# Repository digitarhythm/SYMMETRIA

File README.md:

# SYMMETRIA
TReK 40Plus SYMMETRIA KiCAD Project

[Firmware repository](https://github.com/digitarhythm/qmk_firmware/tree/digitarhythm/keyboards/trek/symmetria)

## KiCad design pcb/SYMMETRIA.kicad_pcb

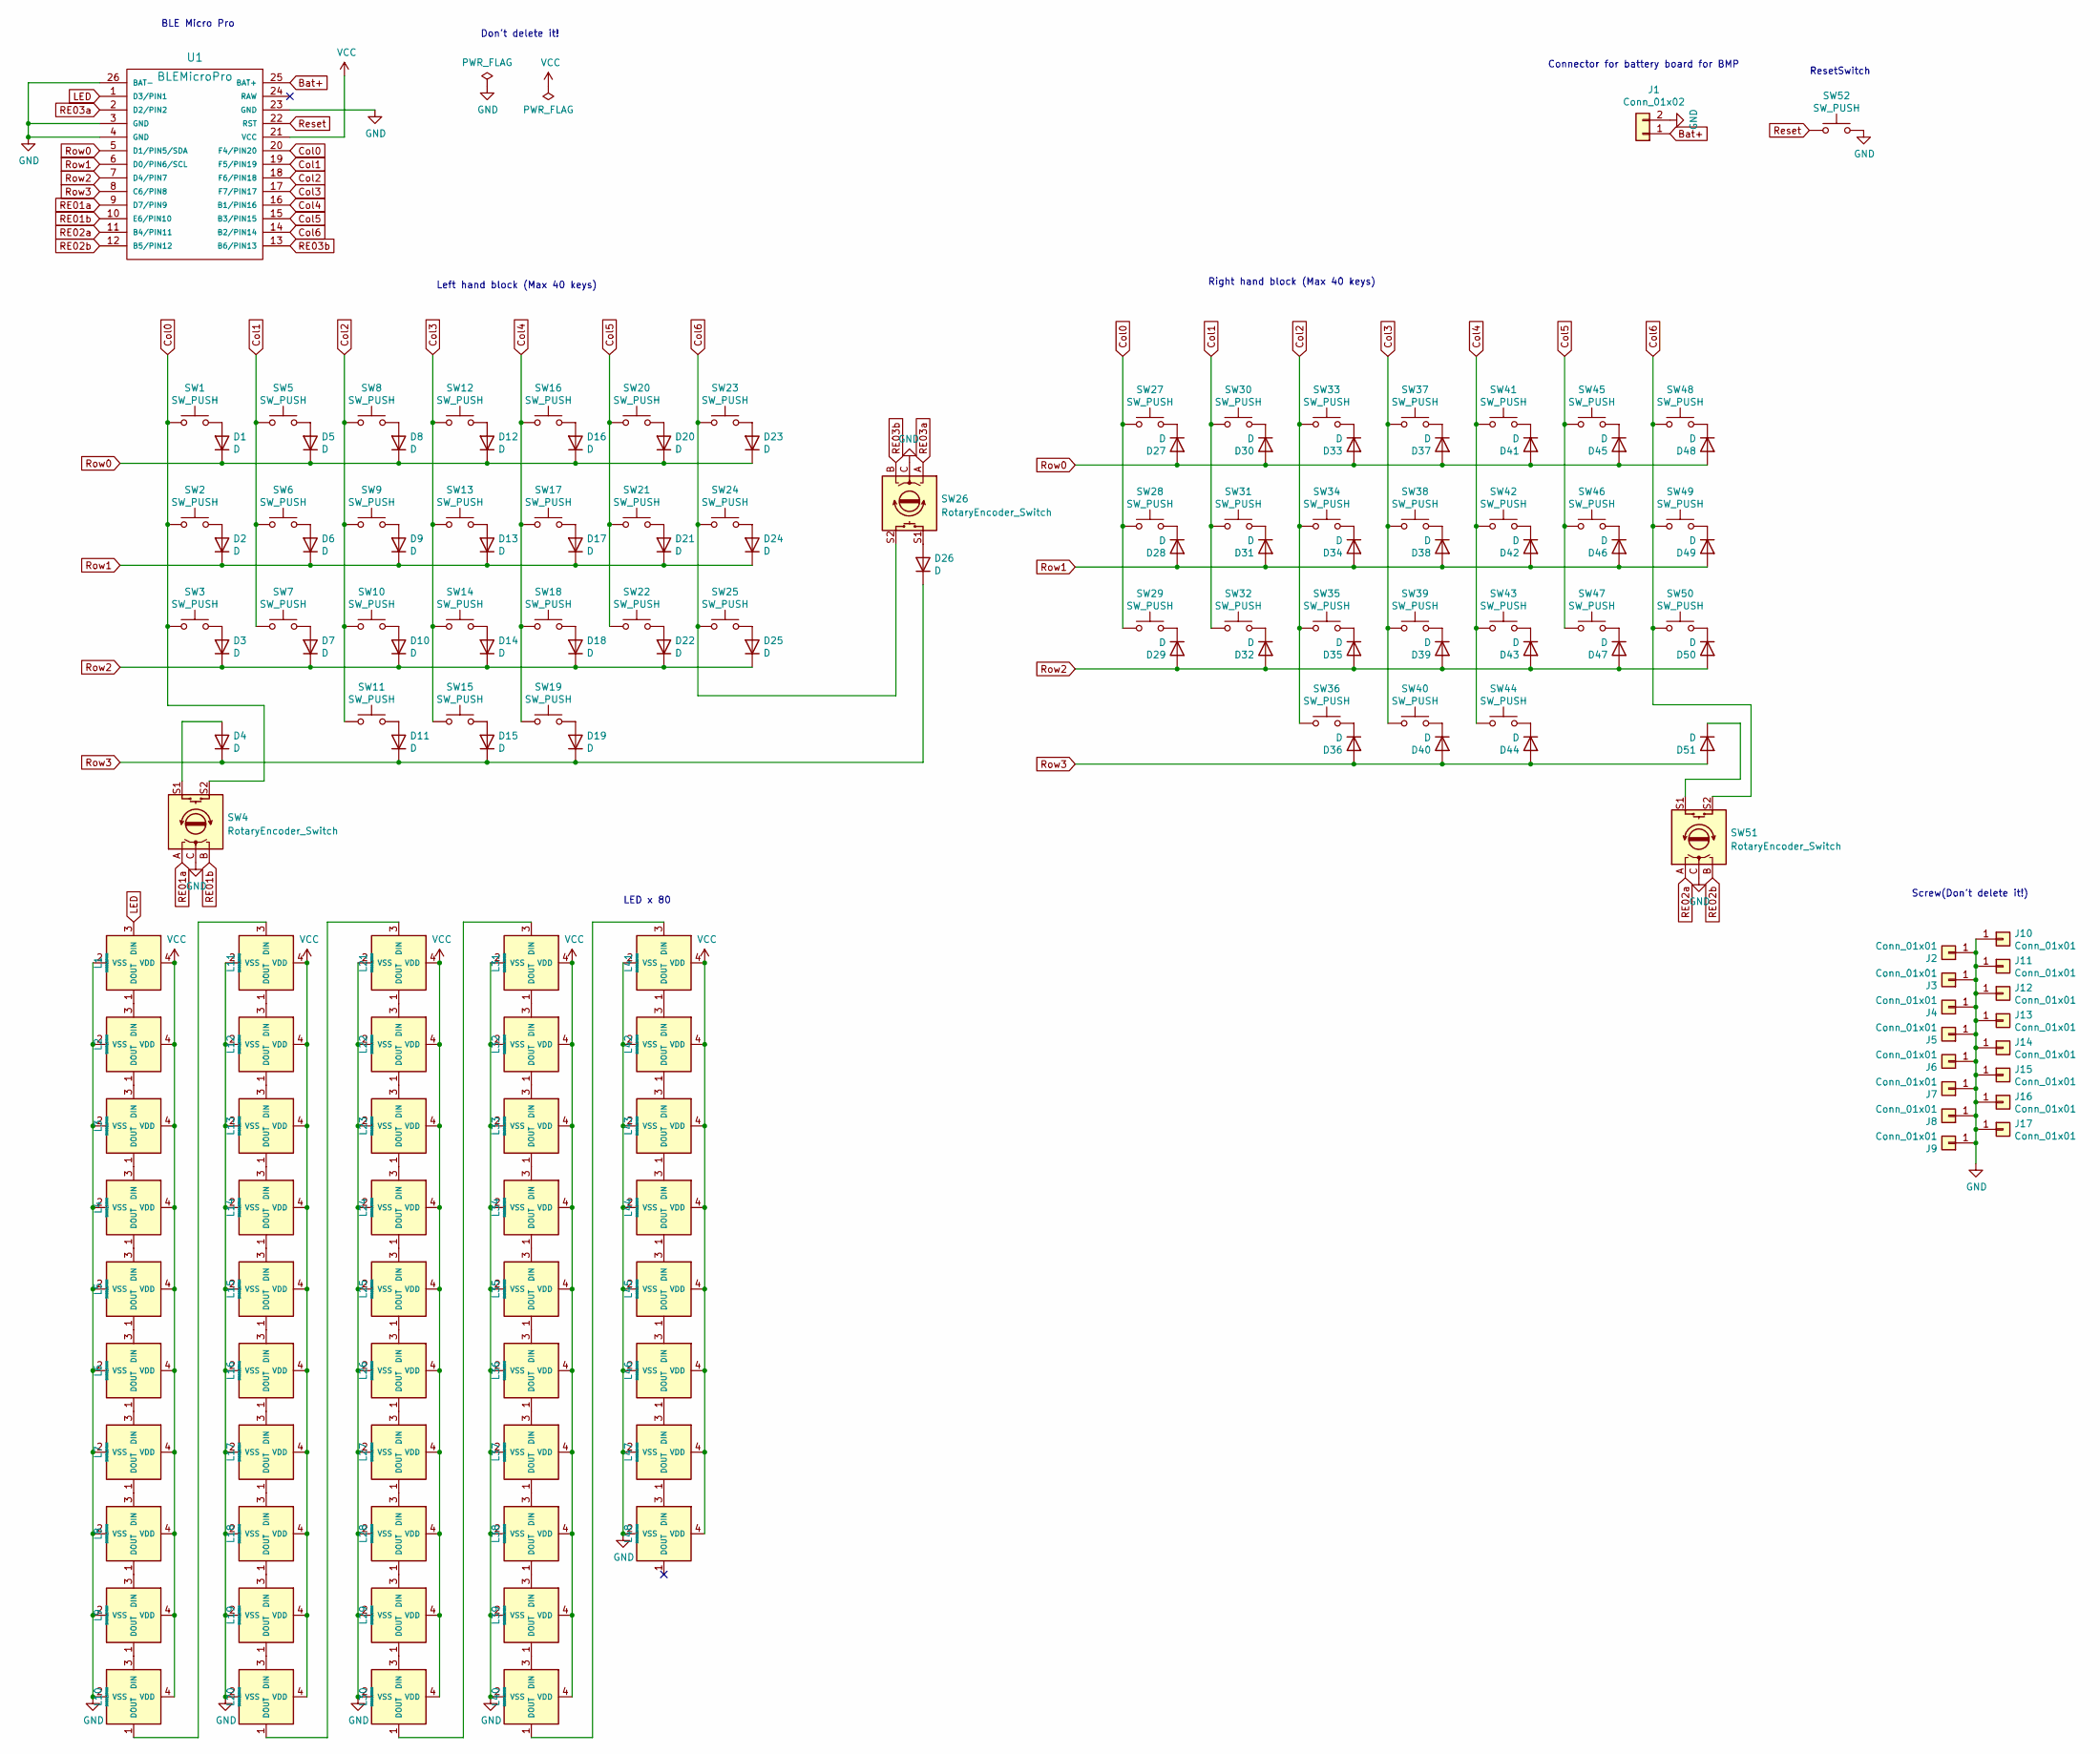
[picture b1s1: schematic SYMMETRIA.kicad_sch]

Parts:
D1, D2, D3, D4, D5, D6, D7, D8, D9, D10, D11, D12, D13, D14, D15, D16, D17, D18, D19, D20, D21, D22, D23, D24, D25, D26, D27, D28, D29, D30, D31, D32, D33, D34, D35, D36, D37, D38, D39, D40, D41, D42, D43, D44, D45, D46, D47, D48, D49, D50, D51: D; Diode_SMD
J1: Conn_01x02; Battery_XH2.5_GL_PCB
J2, J3, J4, J5, J6, J7: Conn_01x01; m2_Screw_Hole_EdgeCuts
J8, J9, J10, J11, J12, J13, J14, J15, J16, J17: Conn_01x01; m2_Screw_Hole_Fab
L1, L2, L3, L4, L5, L6, L7, L8, L9, L10, L11, L12, L13, L14, L15, L16, L17, L18, L19, L20, L21, L22, L23, L24, L25, L26, L27, L28, L29, L30, L31, L32, L33, L34, L35, L36, L37, L38, L39, L40, L41, L42, L43, L44, L45, L46, L47, L48: SK6812MINI; LED_SK6812MINI-E_BL
SW1, SW5, SW6, SW7, SW8, SW9, SW10, SW12, SW13, SW14, SW16, SW17, SW18, SW20, SW21, SW22, SW23, SW24, SW25, SW27, SW28, SW29, SW30, SW31, SW32, SW33, SW34, SW35, SW37, SW38, SW39, SW41, SW42, SW43, SW45, SW46, SW47, SW48: SW_PUSH; CherryMX_Hotswap_1u
SW2, SW11, SW19, SW36, SW44, SW49: SW_PUSH; CherryMX_Hotswap_1.25u
SW3, SW15, SW40, SW50: SW_PUSH; CherryMX_Hotswap_1.75u
SW4, SW51: RotaryEncoder_Switch; RotaryEncoder_EC12E
SW26: RotaryEncoder_Switch; SW_Cherry_MX_1.00u_Kailh_EC12
SW52: SW_PUSH; ResetSW
U1: BLEMicroPro; Micon_BMP_GL

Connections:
Bat+: J1.1, U1.25 (BAT+)
Col0: SW1.1, SW2.1, SW3.1, SW4.S2, SW27.1, SW28.1, SW29.1, U1.20 (F4/PIN20)
Col1: SW5.1, SW6.1, SW7.1, SW30.1, SW31.1, SW32.1, U1.19 (F5/PIN19)
Col2: SW8.1, SW9.1, SW10.1, SW11.1, SW33.1, SW34.1, SW35.1, SW36.1, U1.18 (F6/PIN18)
Col3: SW12.1, SW13.1, SW14.1, SW15.1, SW37.1, SW38.1, SW39.1, SW40.1, U1.17 (F7/PIN17)
Col4: SW16.1, SW17.1, SW18.1, SW19.1, SW41.1, SW42.1, SW43.1, SW44.1, U1.16 (B1/PIN16)
Col5: SW20.1, SW21.1, SW22.1, SW45.1, SW46.1, SW47.1, U1.15 (B3/PIN15)
Col6: SW23.1, SW24.1, SW25.1, SW26.S2, SW48.1, SW49.1, SW50.1, SW51.S2, U1.14 (B2/PIN14)
GND: J1.2, J2.1, J3.1, J4.1, J5.1, J6.1, J7.1, J8.1, J9.1, J10.1, J11.1, J12.1, J13.1, J14.1, J15.1, J16.1, J17.1, L1.2 (VSS), L2.2 (VSS), L3.2 (VSS), L4.2 (VSS), L5.2 (VSS), L6.2 (VSS), L7.2 (VSS), L8.2 (VSS), L9.2 (VSS), L10.2 (VSS), L11.2 (VSS), L12.2 (VSS), L13.2 (VSS), L14.2 (VSS), L15.2 (VSS), L16.2 (VSS), L17.2 (VSS), L18.2 (VSS), L19.2 (VSS), L20.2 (VSS), L21.2 (VSS), L22.2 (VSS), L23.2 (VSS), L24.2 (VSS), L25.2 (VSS), L26.2 (VSS), L27.2 (VSS), L28.2 (VSS), L29.2 (VSS), L30.2 (VSS), L31.2 (VSS), L32.2 (VSS), L33.2 (VSS), L34.2 (VSS), L35.2 (VSS), L36.2 (VSS), L37.2 (VSS), L38.2 (VSS), L39.2 (VSS), L40.2 (VSS), L41.2 (VSS), L42.2 (VSS), L43.2 (VSS), L44.2 (VSS), L45.2 (VSS), L46.2 (VSS), L47.2 (VSS), L48.2 (VSS), SW4.C, SW26.C, SW51.C, SW52.2, U1.3 (GND), U1.4 (GND), U1.23 (GND), U1.26 (BAT-)
LED: L1.3 (DIN), U1.1 (D3/PIN1)
unnamed: D1.2 (A), SW1.2
unnamed: D2.2 (A), SW2.2
unnamed: D3.2 (A), SW3.2
unnamed: D4.2 (A), SW4.S1
unnamed: D5.2 (A), SW5.2
unnamed: D6.2 (A), SW6.2
unnamed: D7.2 (A), SW7.2
unnamed: D8.2 (A), SW8.2
unnamed: D9.2 (A), SW9.2
unnamed: D10.2 (A), SW10.2
unnamed: D11.2 (A), SW11.2
unnamed: D12.2 (A), SW12.2
unnamed: D13.2 (A), SW13.2
unnamed: D14.2 (A), SW14.2
unnamed: D15.2 (A), SW15.2
unnamed: D16.2 (A), SW16.2
unnamed: D17.2 (A), SW17.2
unnamed: D18.2 (A), SW18.2
unnamed: D19.2 (A), SW19.2
unnamed: D20.2 (A), SW20.2
unnamed: D21.2 (A), SW21.2
unnamed: D22.2 (A), SW22.2
unnamed: D23.2 (A), SW23.2
unnamed: D24.2 (A), SW24.2
unnamed: D25.2 (A), SW25.2
unnamed: D26.2 (A), SW26.S1
unnamed: D27.1 (K), SW27.2
unnamed: D28.1 (K), SW28.2
unnamed: D29.1 (K), SW29.2
unnamed: D30.1 (K), SW30.2
unnamed: D31.1 (K), SW31.2
unnamed: D32.1 (K), SW32.2
unnamed: D33.1 (K), SW33.2
unnamed: D34.1 (K), SW34.2
unnamed: D35.1 (K), SW35.2
unnamed: D36.1 (K), SW36.2
unnamed: D37.1 (K), SW37.2
unnamed: D38.1 (K), SW38.2
unnamed: D39.1 (K), SW39.2
unnamed: D40.1 (K), SW40.2
unnamed: D41.1 (K), SW41.2
unnamed: D42.1 (K), SW42.2
unnamed: D43.1 (K), SW43.2
unnamed: D44.1 (K), SW44.2
unnamed: D45.1 (K), SW45.2
unnamed: D46.1 (K), SW46.2
unnamed: D47.1 (K), SW47.2
unnamed: D48.1 (K), SW48.2
unnamed: D49.1 (K), SW49.2
unnamed: D50.1 (K), SW50.2
unnamed: D51.1 (K), SW51.S1
unnamed: L1.1 (DOUT), L2.3 (DIN)
unnamed: L2.1 (DOUT), L3.3 (DIN)
unnamed: L3.1 (DOUT), L4.3 (DIN)
unnamed: L4.1 (DOUT), L5.3 (DIN)
unnamed: L5.1 (DOUT), L6.3 (DIN)
unnamed: L6.1 (DOUT), L7.3 (DIN)
unnamed: L7.1 (DOUT), L8.3 (DIN)
unnamed: L8.1 (DOUT), L9.3 (DIN)
unnamed: L10.1 (DOUT), L11.3 (DIN)
unnamed: L9.1 (DOUT), L10.3 (DIN)
unnamed: L11.1 (DOUT), L12.3 (DIN)
unnamed: L12.1 (DOUT), L13.3 (DIN)
unnamed: L13.1 (DOUT), L14.3 (DIN)
unnamed: L14.1 (DOUT), L15.3 (DIN)
unnamed: L15.1 (DOUT), L16.3 (DIN)
unnamed: L16.1 (DOUT), L17.3 (DIN)
unnamed: L17.1 (DOUT), L18.3 (DIN)
unnamed: L18.1 (DOUT), L19.3 (DIN)
unnamed: L19.1 (DOUT), L20.3 (DIN)
unnamed: L20.1 (DOUT), L21.3 (DIN)
unnamed: L21.1 (DOUT), L22.3 (DIN)
unnamed: L22.1 (DOUT), L23.3 (DIN)
unnamed: L23.1 (DOUT), L24.3 (DIN)
unnamed: L24.1 (DOUT), L25.3 (DIN)
unnamed: L25.1 (DOUT), L26.3 (DIN)
unnamed: L26.1 (DOUT), L27.3 (DIN)
unnamed: L27.1 (DOUT), L28.3 (DIN)
unnamed: L28.1 (DOUT), L29.3 (DIN)
unnamed: L29.1 (DOUT), L30.3 (DIN)
unnamed: L30.1 (DOUT), L31.3 (DIN)
unnamed: L31.1 (DOUT), L32.3 (DIN)
unnamed: L32.1 (DOUT), L33.3 (DIN)
unnamed: L33.1 (DOUT), L34.3 (DIN)
unnamed: L34.1 (DOUT), L35.3 (DIN)
unnamed: L35.1 (DOUT), L36.3 (DIN)
unnamed: L36.1 (DOUT), L37.3 (DIN)
unnamed: L37.1 (DOUT), L38.3 (DIN)
unnamed: L38.1 (DOUT), L39.3 (DIN)
unnamed: L39.1 (DOUT), L40.3 (DIN)
unnamed: L40.1 (DOUT), L41.3 (DIN)
unnamed: L41.1 (DOUT), L42.3 (DIN)
unnamed: L42.1 (DOUT), L43.3 (DIN)
unnamed: L43.1 (DOUT), L44.3 (DIN)
unnamed: L44.1 (DOUT), L45.3 (DIN)
unnamed: L45.1 (DOUT), L46.3 (DIN)
unnamed: L46.1 (DOUT), L47.3 (DIN)
unnamed: L47.1 (DOUT), L48.3 (DIN)
RE01a: SW4.A, U1.9 (D7/PIN9)
RE01b: SW4.B, U1.10 (E6/PIN10)
RE02a: SW51.A, U1.11 (B4/PIN11)
RE02b: SW51.B, U1.12 (B5/PIN12)
RE03a: SW26.A, U1.2 (D2/PIN2)
RE03b: SW26.B, U1.13 (B6/PIN13)
Reset: SW52.1, U1.22 (RST)
Row0: D1.1 (K), D5.1 (K), D8.1 (K), D12.1 (K), D16.1 (K), D20.1 (K), D23.1 (K), D27.2 (A), D30.2 (A), D33.2 (A), D37.2 (A), D41.2 (A), D45.2 (A), D48.2 (A), U1.5 (D1/PIN5/SDA)
Row1: D2.1 (K), D6.1 (K), D9.1 (K), D13.1 (K), D17.1 (K), D21.1 (K), D24.1 (K), D28.2 (A), D31.2 (A), D34.2 (A), D38.2 (A), D42.2 (A), D46.2 (A), D49.2 (A), U1.6 (D0/PIN6/SCL)
Row2: D3.1 (K), D7.1 (K), D10.1 (K), D14.1 (K), D18.1 (K), D22.1 (K), D25.1 (K), D29.2 (A), D32.2 (A), D35.2 (A), D39.2 (A), D43.2 (A), D47.2 (A), D50.2 (A), U1.7 (D4/PIN7)
Row3: D4.1 (K), D11.1 (K), D15.1 (K), D19.1 (K), D26.1 (K), D36.2 (A), D40.2 (A), D44.2 (A), D51.2 (A), U1.8 (C6/PIN8)
VCC: L1.4 (VDD), L2.4 (VDD), L3.4 (VDD), L4.4 (VDD), L5.4 (VDD), L6.4 (VDD), L7.4 (VDD), L8.4 (VDD), L9.4 (VDD), L10.4 (VDD), L11.4 (VDD), L12.4 (VDD), L13.4 (VDD), L14.4 (VDD), L15.4 (VDD), L16.4 (VDD), L17.4 (VDD), L18.4 (VDD), L19.4 (VDD), L20.4 (VDD), L21.4 (VDD), L22.4 (VDD), L23.4 (VDD), L24.4 (VDD), L25.4 (VDD), L26.4 (VDD), L27.4 (VDD), L28.4 (VDD), L29.4 (VDD), L30.4 (VDD), L31.4 (VDD), L32.4 (VDD), L33.4 (VDD), L34.4 (VDD), L35.4 (VDD), L36.4 (VDD), L37.4 (VDD), L38.4 (VDD), L39.4 (VDD), L40.4 (VDD), L41.4 (VDD), L42.4 (VDD), L43.4 (VDD), L44.4 (VDD), L45.4 (VDD), L46.4 (VDD), L47.4 (VDD), L48.4 (VDD), U1.21 (VCC)

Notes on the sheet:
Left hand block (Max 40 keys)
LED x 80
ResetSwitch
Screw(Don't delete it!)
Don't delete it!
Connector for battery board for BMP
Right hand block (Max 40 keys)
BLE Micro Pro

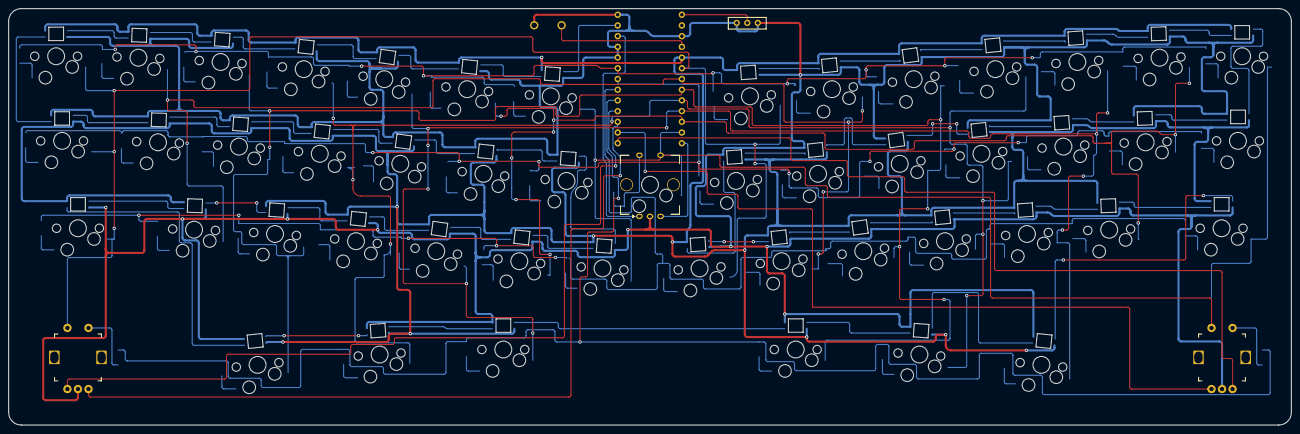
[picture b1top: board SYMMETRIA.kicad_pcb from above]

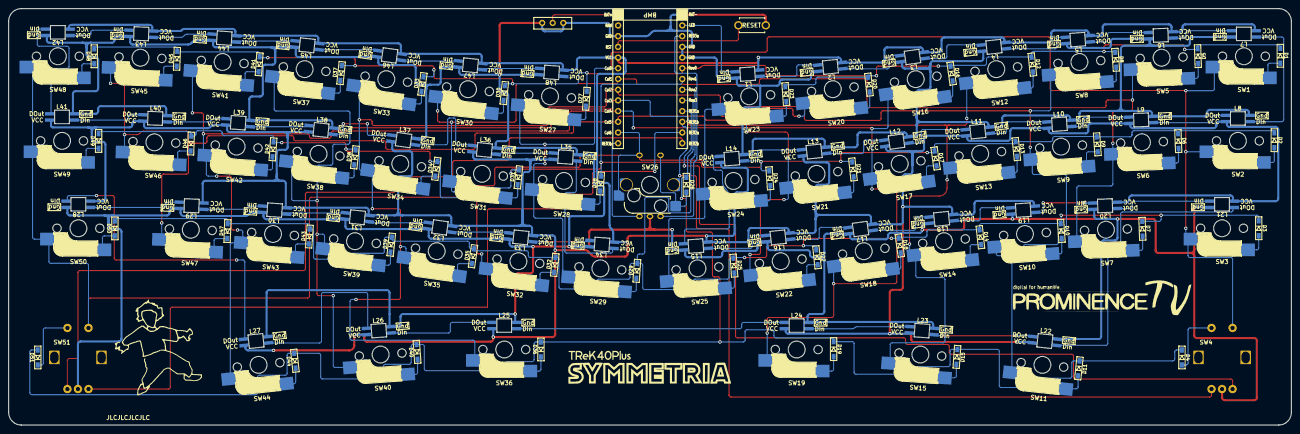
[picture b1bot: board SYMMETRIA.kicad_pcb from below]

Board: 2 copper layers, 304.4 x 98.8 mm, 156 parts (3 on the bottom side), 120 nets.

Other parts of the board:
G000, G001, G002: LOGO

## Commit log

2023-09-26 update README.md for SYMMETRIA
2024-01-30 update licence file
2024-02-25 Update LICENCE
